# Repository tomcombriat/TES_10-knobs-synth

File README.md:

# TES - 10 knobs synth
T. Combriat 

10 knobs synths are simple synthesizers based on [Mozzi](https://github.com/sensorium/Mozzi) using STM32 blue pill with 10 knobs. Different versions are available:

  - 10knobs_mono_24bits_MCP4822 is a mono synth built around the MCP4822 dual DAC, with theoritical 24 bits resolution (in practice, around 14/16 bits get outside the noise, but that is already quite a lot). It can easily be turned into a stereo synth with 12bits on each channel.
  - 10knobs_mono_16bits_PT8211 is a mono synth built around the PT8211 dual DAC, with theoritical 16 bits resolution. This one can easily be upgraded to a stereo version: only one channel of the PT8211 is used here.

The aim of this serie is to provide a quite fixed hardware which can be used for different synthesis methods.

***

### Hardware
These synthesizers have: 
* MIDI input and thru
* 10 knobs for controlling parameters (thus the name), note that one is hardwired for logarithmic volume control
* 6.35mm analog (DAC) audio output (mono/stereo)
* standalone power from ~~3~~ 4 AA batteries. This ensures cleaner sound thanks to very stable power lines. This has been changed from 3 to 4 in order to get some room over the signal level for the op-amps.

PCBs for the chip are single faced and can be easily made if one is able to make 220 microns wide tracks. The masks are provided in the hardware folders for each version.

***

### Programming
These synths can be programmed like any other STM32 pills using USB to serial converter. Native USB will usually not work. You will  also need a rather new version of the Arduino IDE with Mozzi installed and modify Mozzi in accordance with the beginning of the sketch or use the [TES forked version of Mozzi](https://github.com/tomcombriat/Mozzi/tree/TES-stable).

As a general matter, the programs tries to use the most of the chip, so it usually needs to be compiled with -O2 or -O3 with the maximum overclock. As the chip is not confined, the OC does not pose any problem.

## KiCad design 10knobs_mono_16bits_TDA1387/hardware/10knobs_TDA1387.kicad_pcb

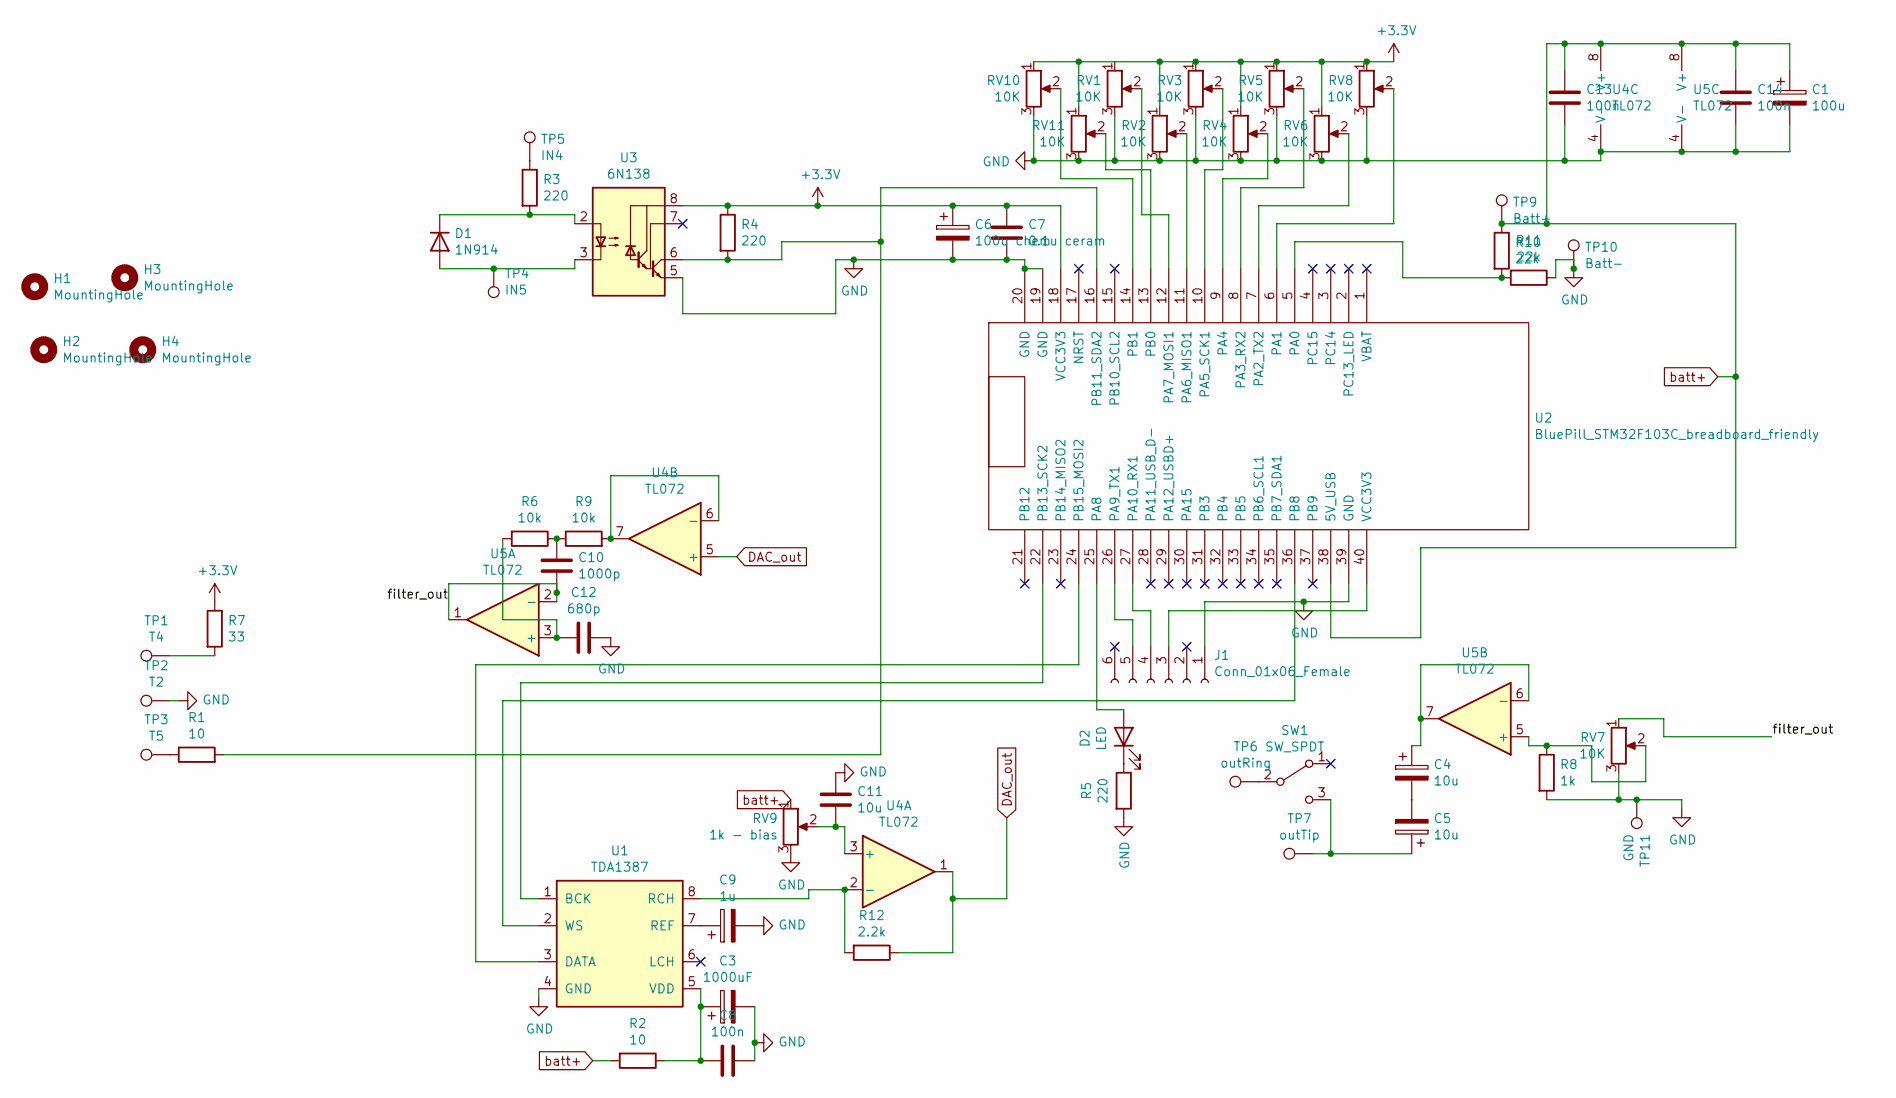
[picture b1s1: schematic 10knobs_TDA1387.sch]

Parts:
C1: 100u; CP_Radial_D5.0mm_P2.50mm
C3: 1000uF; CP_Radial_D7.5mm_P2.50mm
C4, C5, C11: 10u; CP_Radial_D5.0mm_P2.50mm
C6: 100u chem; CP_Radial_D5.0mm_P2.50mm
C7: 0.1u ceram; C_Disc_D3.0mm_W2.0mm_P2.50mm
C8: 100n; C_Disc_D3.0mm_W2.0mm_P2.50mm
C9: 1u; CP_Radial_D5.0mm_P2.50mm
C10: 1000p; C_Disc_D5.0mm_W2.5mm_P2.50mm
C12: 680p; C_Disc_D5.0mm_W2.5mm_P2.50mm
C13, C14: 100n; C_Disc_D5.0mm_W2.5mm_P2.50mm
D1: 1N914; D_DO-35_SOD27_P7.62mm_Horizontal
D2: LED; LED_D3.0mm
H1, H2, H3, H4: MountingHole; MountingHole_3.2mm_M3_ISO7380_Pad
J1: Conn_01x06_Female; PinHeader_1x06_P2.54mm_Vertical
R1, R2: 10; R_Axial_DIN0207_L6.3mm_D2.5mm_P7.62mm_Horizontal
R3, R4, R5: 220; R_Axial_DIN0207_L6.3mm_D2.5mm_P7.62mm_Horizontal
R6, R9: 10k; R_Axial_DIN0207_L6.3mm_D2.5mm_P7.62mm_Horizontal
R7: 33; R_Axial_DIN0207_L6.3mm_D2.5mm_P7.62mm_Horizontal
R8: 1k; R_Axial_DIN0207_L6.3mm_D2.5mm_P7.62mm_Horizontal
R10, R11: 22k; R_Axial_DIN0207_L6.3mm_D2.5mm_P7.62mm_Horizontal
R12: 2.2k; R_Axial_DIN0207_L6.3mm_D2.5mm_P7.62mm_Horizontal
RV1, RV2, RV3, RV4, RV5, RV6, RV7, RV8, RV10, RV11: 10K; Potentiometer_Alps_RK09K_Single_Vertical
RV9: 1k - bias; Potentiometer_Bourns_3296W_Vertical
SW1: SW_SPDT; PinSocket_1x03_P2.54mm_Vertical
TP1: T4; TestPoint_THTPad_2.5x2.5mm_Drill1.2mm
TP2: T2; TestPoint_THTPad_2.5x2.5mm_Drill1.2mm
TP3: T5; TestPoint_THTPad_2.5x2.5mm_Drill1.2mm
TP4: IN5; TestPoint_THTPad_2.5x2.5mm_Drill1.2mm
TP5: IN4; TestPoint_THTPad_2.5x2.5mm_Drill1.2mm
TP6: outRing; TestPoint_THTPad_2.5x2.5mm_Drill1.2mm
TP7: outTip; TestPoint_THTPad_2.5x2.5mm_Drill1.2mm
TP9: Batt+; TestPoint_THTPad_2.5x2.5mm_Drill1.2mm
TP10: Batt-; TestPoint_THTPad_2.5x2.5mm_Drill1.2mm
TP11: GND; TestPoint_THTPad_2.5x2.5mm_Drill1.2mm
U1: TDA1387; SO-8_3.9x4.9mm_P1.27mm
U2: BluePill_STM32F103C_breadboard_friendly
U3: 6N138; DIP-8_W7.62mm
U4, U5: TL072; DIP-8_W7.62mm_Socket_LongPads

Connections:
+3V3: C6.1, C7.1, R4.1, R7.1, RV1.1, RV2.1, RV3.1, RV4.1, RV5.1, RV6.1, RV8.1, RV10.1, RV11.1, U2.18 (VCC3V3), U3.8 (VCC)
/filter_out: C10.2, RV7.1, U5.1, U5.2 (-)
DAC_out: R12.1, U4.1, U4.5 (+)
GND: C1.2, C3.2, C6.2, C7.2, C8.1, C9.2, C11.1, C12.1, C13.2, C14.2, J1.1, R5.2, R8.2, R11.1, RV1.3, RV2.3, RV3.3, RV4.3, RV5.3, RV6.3, RV7.3, RV8.3, RV9.3, RV10.3, RV11.3, TP2.1, TP10.1, TP11.1, U1.4 (GND), U2.19 (GND), U2.20 (GND), U2.39 (GND), U3.5 (GND), U4.4 (V-), U5.4 (V-)
unnamed: C3.1, C8.2, R2.1, U1.5 (VDD)
unnamed: C4.1, U5.6 (-), U5.7
unnamed: C4.2, C5.2
unnamed: C5.1, SW1.3 (C), TP7.1
unnamed: C9.1, U1.7 (REF)
unnamed: C10.1, R6.1, R9.1
unnamed: C11.2, RV9.2, U4.3 (+)
unnamed: C12.2, R6.2, U5.3 (+)
unnamed: D1.1 (K), R3.2, U3.2 (C1)
unnamed: D1.2 (A), TP4.1, U3.3 (C2)
unnamed: D2.1 (K), R5.1
unnamed: D2.2 (A), U2.25 (PA8)
unnamed: J1.3, U2.40 (VCC3V3)
unnamed: J1.4, U2.27 (PA10_RX1)
unnamed: J1.5, U2.26 (PA9_TX1)
unnamed: R1.1, TP3.1
unnamed: R1.2, R4.2, U2.16 (PB11_SDA2), U3.6 (VO2)
unnamed: R3.1, TP5.1
unnamed: R7.2, TP1.1
unnamed: R8.1, RV7.2, U5.5 (+)
unnamed: R9.2, U4.6 (-), U4.7
unnamed: R10.2, R11.2, U2.5 (PA0)
unnamed: R12.2, U1.8 (RCH), U4.2 (-)
unnamed: RV1.2, U2.12 (PA7_MOSI1)
unnamed: RV2.2, U2.11 (PA6_MISO1)
unnamed: RV3.2, U2.10 (PA5_SCK1)
unnamed: RV4.2, U2.9 (PA4)
unnamed: RV5.2, U2.8 (PA3_RX2)
unnamed: RV6.2, U2.7 (PA2_TX2)
unnamed: RV8.2, U2.6 (PA1)
unnamed: RV10.2, U2.14 (PB1)
unnamed: RV11.2, U2.13 (PB0)
unnamed: SW1.2 (B), TP6.1
unnamed: U1.1 (BCK), U2.22 (PB13_SCK2)
unnamed: U1.2 (WS), U2.36 (PB8)
unnamed: U1.3 (DATA), U2.24 (PB15_MOSI2)
batt+: C1.1, C13.1, C14.1, R2.2, R10.1, RV9.1, TP9.1, U2.38 (5V_USB), U4.8 (V+), U5.8 (V+)

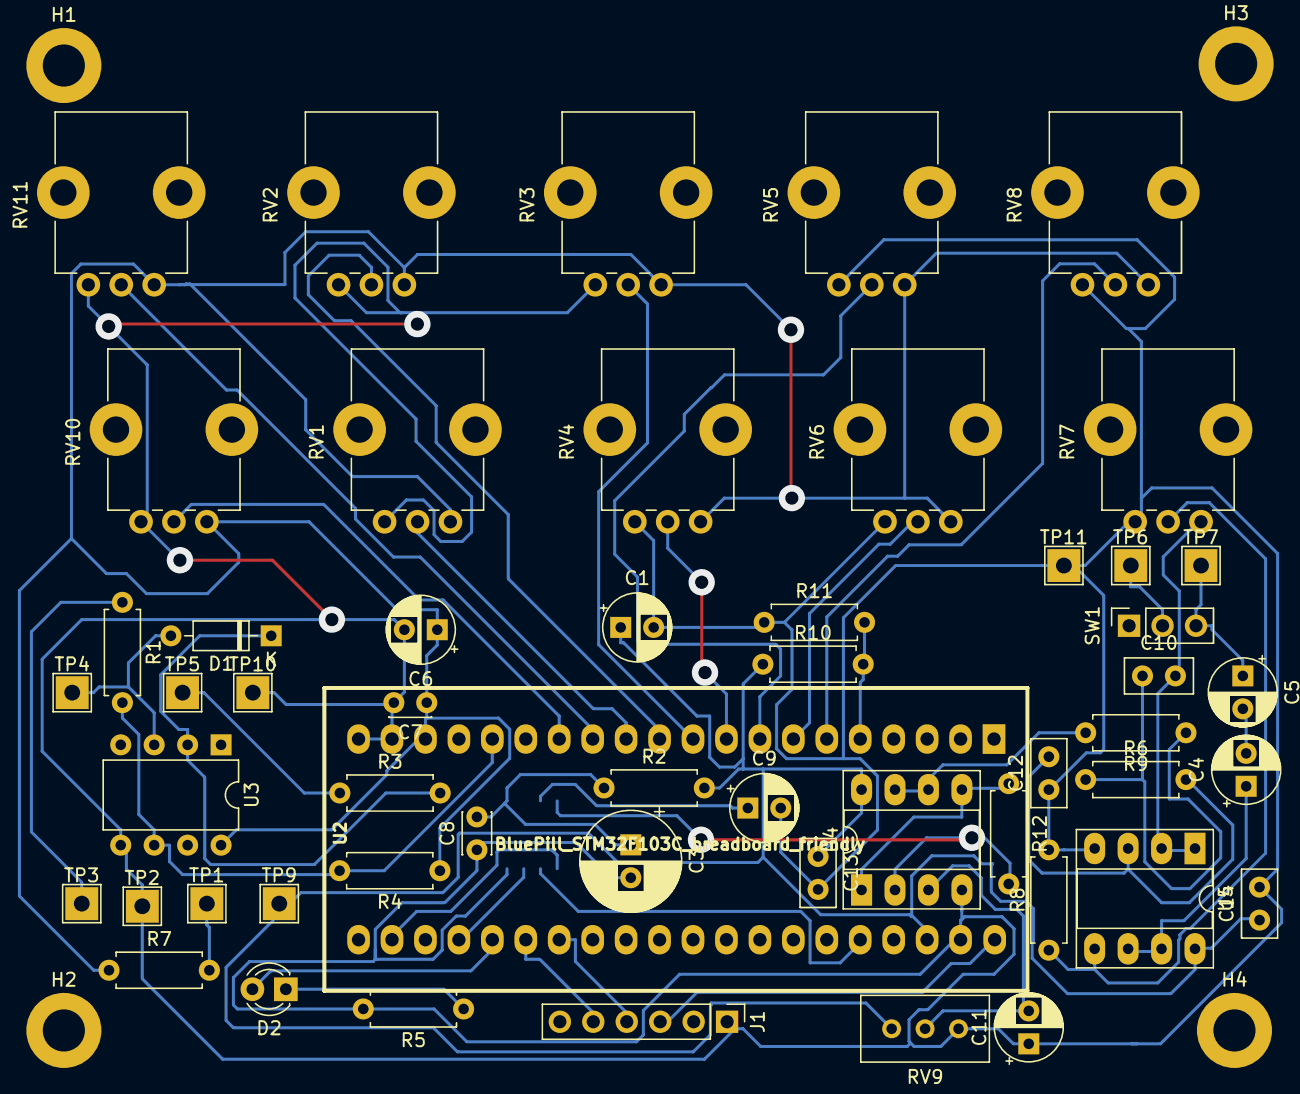
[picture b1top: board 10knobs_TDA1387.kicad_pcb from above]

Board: 2 copper layers, 59 parts (1 on the bottom side), 41 nets.

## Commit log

2020-08-22 Upgraded output on PCB: OA added, Condensators also
2020-08-23 Added PCB, final corrections
2020-08-30 Cleanup, created separated hardware and software folders
2020-08-30 Added tests sketches
2020-08-30 Corrected schematic and PCB
2020-08-30 Adapted hardware check to the 2 extras pot
2020-08-30 Added roughtly adapted version of XORAND
2020-09-01 Added func to extra pots
2020-09-01 Successfully implemented breath_on_volume pot
2020-09-06 Adapted chords timings, test on filter behavior. Added comments.
2020-09-07 Removed too much digital overdrive
2020-09-11 Increased control Rate, decrease breath smooth
2020-10-04 Added trimming sketch
2020-10-08 Corrected wrong behavior with chords
2020-12-10 Version 2.1, with correct MIDI and more stab cap
2020-12-11 Changed name
2020-12-11 Updated PCB
2020-12-28 Added readme in the softwares
2020-12-28 Added new version of synth to readme
2020-12-28 Edited schematic for mono PT8211
2020-12-28 Updated 10k MCP4822 mono
2020-12-29 Completed mono PT8211 PCB
2020-12-29 Removed auto saves
2020-12-30 Adjusted lpf
2020-12-30 Update readme.
2020-12-30 Updated the readme
2020-12-30 Added readme for 10k pt8211
2020-12-30 Added details in readme
2021-01-18 Added PCB, removed unneeded files
2021-04-11 Added copy of XORand
2021-05-03 Initial change for PT8211 DAC
2021-05-14 Added non-aliased version of XORAND
2021-05-14 Corrected original XORAND
2021-05-14 Set phase is valid only when an oscillator has been selected, hence not at init
2021-05-15 Correct meta version
2021-05-23 Working version of the XORAND for PT8211
2021-05-23 Changed ratio between breath and WT, all WT are 512 for synthesis
2021-05-23 RM temp file
2021-05-23 Adjusted shifts for (hopefully) better precision
2021-05-24 Added a stab capacitor on the DAC
2021-05-30 Breath on cutoff now covers the full range
2021-08-23 Test for HQ breath
2021-08-23 Working like before with HQ breath
2021-08-25 Implemented with LowPassFilter16
2021-08-26 Smoother transitions with 14 bits breath
2021-09-20 Correction of HQ midi
2021-09-20 Damn break
2021-09-21 upgradd smoothing of midi inputs
2021-12-03 test
2021-12-14 Preliminary work with TDA1387
2021-12-27 Finished routing
2022-05-07 Improvment of phases
2022-05-15 Moved things in provision for v2
2022-06-26 Moved to seperate folders
2022-06-26 Added a triming soft for the v2
2022-06-28 Moving it was a mistake
2022-06-28 Prototype of digital senap sax synth
2022-06-28 Started stripping off XORAND for digital_senap
2022-07-09 First sound design, works with no enveloppes
2022-07-10 Enveloppes and filter added
2022-07-10 Increased polyphony
2022-07-12 Chords in decay not following higher breath anymore
2022-07-12 Split pot test
2022-07-12 Cleanup, opti
2022-07-12 Last potard affected to breath on ring modulator
2022-07-19 Anti-aliasing throught LUT implemented
2022-07-21 Added one more bit for mod to carrier ratio (allows for .5 and integer values) Added test for dithering output
2022-07-23 Corrected same than previous on XORAND
2022-07-23 Corrected chords which were coming back after being shut down
2022-07-23 Added dithering to XORAND
2022-07-24 Fixed PB on digital senap
2022-08-10 Starting keyboard version of XORAND mk3
2022-08-10 Starting adapting to keyboard
2022-08-15 First sounding version of XORAND keyboard v3, added FM
2022-08-16 Interveted modulation wheel and pot, the pot as more precision hence more interesting for mod_to_carrier_ratio
2022-09-16 Added missing file
2022-09-20 Fixed phases problems between notes
2022-10-26 Updated breath on volume
2022-10-26 Corrected bit reduc
2022-10-27 Improved breath on vol with LUT
2022-11-09 More sensitive to small volume, in accordance with sax modifications
2022-11-09 Udpate to more sensitive breath
2022-11-09 Adapted noteOns to low velocities
2022-11-09 Fixed indentation
2022-11-10 Improved 14bits breath
2022-11-14 Adapted xorand on new breath sens
2023-04-29 Fix compilation
2023-04-29 Update to new stm32duino
2023-05-03 Fixed static allocation of oscillators
2023-05-03 updates after tests
2023-05-06 Added compressor to digital senap for helping clarity of chords
2023-05-07 Update DigitalSenap with more headroom for testing
